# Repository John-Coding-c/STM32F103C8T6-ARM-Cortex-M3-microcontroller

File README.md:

# STM32 PCB

STM32F103C8T6 breakout board — USB-powered, SWD/UART/I2C headers, 41 × 31 mm, 2 layers. KiCad 10.

## Specs

- **MCU:** STM32F103C8T6, Cortex-M3 @ 72 MHz, 64 KB flash, 20 KB RAM, LQFP-48
- **Clock:** 16 MHz HSE crystal (3225), 2× 10 pF load caps
- **Power:** 5 V USB VBUS → AMS1117-3.3 LDO (1 A, SOT-223), 22 µF in/out
- **Decoupling:** 5× 100 nF (0402) + 10 µF bulk on VDD
- **VDDA:** filtered via 120 Ω ferrite bead + 10 nF + 1 µF
- **USB:** full-speed device on PA11/PA12, 1.5 kΩ D+ pull-up
- **Boot:** SPDT slide switch on BOOT0 via 10 kΩ
- **I2C pull-ups:** 1.5 kΩ to 3.3 V
- **Indicator:** red power LED (0603), 1.5 kΩ (~1 mA)
- **Mounting:** 4× 2.1 mm holes (M2), 3 mm corner radius

## Schematic

## PCB

| Parameter | Value |
| --- | --- |
| Size | 41 × 31 mm |
| Stackup | 2-layer, 1.6 mm FR4, 35 µm Cu |
| Bottom layer | Solid GND pour |
| Min track / clearance | 0.2 / 0.2 mm |
| Power tracks | 0.5 mm |
| Vias | 0.6–0.7 mm / 0.3 mm drill |
| Components | 28 parts + 4 mounting holes, all top side |
| Passives | 0402 / 0603 / 0805 |

## Pinout

All headers 1×4, 2.54 mm. Pin 1 = square pad.

| Header | Pin 1 | Pin 2 | Pin 3 | Pin 4 |
| --- | --- | --- | --- | --- |
| SWD (J3) | 3.3 V | SWDIO / PA13 | SWCLK / PA14 | GND |
| UART (J1) | 3.3 V | TX / PB6 | RX / PB7 | GND |
| I2C (J2) | 3.3 V | SCL / PB10 | SDA / PB11 | GND |

- UART uses remapped USART1 — set `AFIO_MAPR_USART1_REMAP` in firmware.

## BOM

| Ref | Qty | Value | Package |
| --- | --- | --- | --- |
| U2 | 1 | STM32F103C8T6 | LQFP-48 |
| U1 | 1 | AMS1117-3.3 | SOT-223 |
| Y1 | 1 | 16 MHz | 3225-4 |
| J4 | 1 | Micro-USB B (Würth 629105150521) | SMD |
| J1–J3 | 3 | 1×4 header | 2.54 mm THT |
| SW1 | 1 | SPDT slide (C&K PCM12) | SMD |
| D1 | 1 | Red LED | 0603 |
| FB1 | 1 | 120 Ω ferrite | 0603 |
| C1, C2 | 2 | 22 µF | 0805 |
| C3 | 1 | 10 µF | 0603 |
| C4, C6, C7, C9, C10 | 5 | 100 nF | 0402 |
| C5, C8 | 2 | 10 pF | 0402 |
| C11 | 1 | 10 nF | 0402 |
| C12, C13 | 2 | 1 µF | 0402 |
| R1–R3, R5 | 4 | 1.5 kΩ | 0402 |
| R4 | 1 | 10 kΩ | 0402 |

- LCSC part numbers included — ready for JLCPCB assembly.
- Full files: `STM32-BOM.csv`, `STM32-all-pos.csv`

## Files

```
STM32.kicad_pro / .kicad_sch / .kicad_pcb   KiCad project
STM32-BOM.csv, STM32-all-pos.csv            BOM + pick-and-place
629105150521 (rev1).stp                     USB connector 3D model
manufracture/                               Gerbers + drill
images/                                     Render + schematic
```

## Programming

- **SWD:** ST-Link V2 → J3. Flash with STM32CubeProgrammer or OpenOCD.
- **Bootloader:** BOOT0 = 1 enters the ROM bootloader.

## License

[CERN-OHL-P-2.0](https://ohwr.org/cern_ohl_p_v2.txt) — permissive open hardware license. See `LICENSE`.

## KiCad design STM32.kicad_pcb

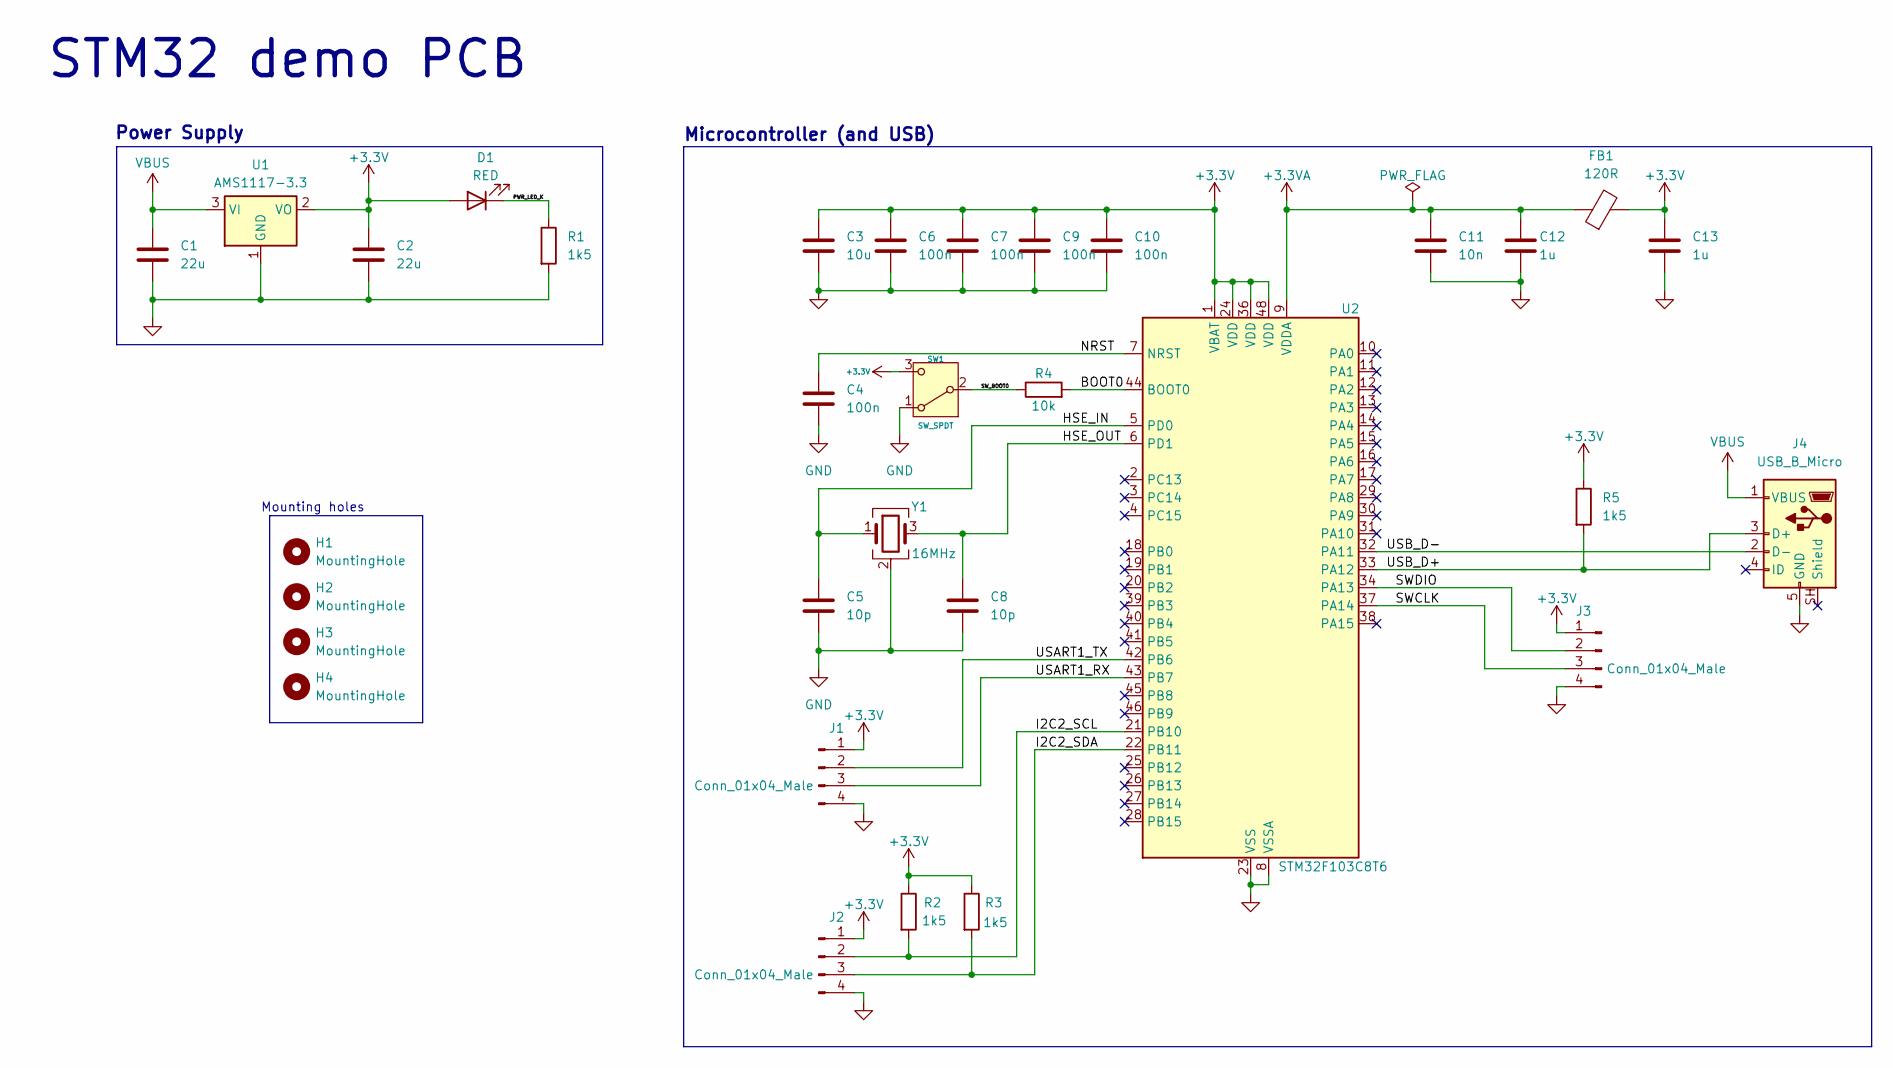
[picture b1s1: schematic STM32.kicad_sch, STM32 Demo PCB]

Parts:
C1, C2: 22u; C_0805_2012Metric; LCSC C45783
C3: 10u; C_0603_1608Metric; LCSC C19702
C4, C6, C7, C9, C10: 100n; C_0402_1005Metric; LCSC C1525
C5, C8: 10p; C_0402_1005Metric; LCSC C32949
C11: 10n; C_0402_1005Metric; LCSC C15195
C12, C13: 1u; C_0402_1005Metric; LCSC C52923
D1: RED; LED_0603_1608Metric; LCSC C2286
FB1: 120R; L_0603_1608Metric
H1, H2, H3, H4: MountingHole; MountingHole_2.1mm
J1, J2, J3: Conn_01x04_Male; PinHeader_1x04_P2.54mm_Vertical
J4: USB_B_Micro; USB_Micro-B_Wuerth_629105150521
R1, R2, R3, R5: 1k5; R_0402_1005Metric; LCSC C25867
R4: 10k; R_0402_1005Metric; LCSC C25744
SW1: SW_SPDT; SW_SPDT_PCM12; LCSC C221841
U1: AMS1117-3.3; SOT-223-3_TabPin2; LCSC C6186
U2: STM32F103C8T6; LQFP-48_7x7mm_P0.5mm; LCSC C8734
Y1: 16MHz; Crystal_SMD_3225-4Pin_3.2x2.5mm; LCSC C13738

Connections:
+3.3V: C2.1, C3.1, C6.1, C7.1, C9.1, C10.1, C13.1, D1.2 (A), FB1.2, J1.1, J2.1, J3.1, R2.1, R3.1, R5.1, SW1.3 (C), U1.2 (VO), U2.1 (VBAT), U2.24 (VDD), U2.36 (VDD), U2.48 (VDD)
+3.3VA: C11.1, C12.1, FB1.1, U2.9 (VDDA)
/BOOT0: R4.2, U2.44 (BOOT0)
/HSE_IN: C5.2, U2.5 (PD0), Y1.1
/HSE_OUT: C8.2, U2.6 (PD1), Y1.3
/I2C2_SCL: J2.2, R2.2, U2.21 (PB10)
/I2C2_SDA: J2.3, R3.2, U2.22 (PB11)
/NRST: C4.1, U2.7 (NRST)
/PWR_LED_K: D1.1 (K), R1.1
/SWCLK: J3.3, U2.37 (PA14)
/SWDIO: J3.2, U2.34 (PA13)
/SW_BOOT0: R4.1, SW1.2 (B)
/USART1_RX: J1.3, U2.43 (PB7)
/USART1_TX: J1.2, U2.42 (PB6)
/USB_D+: J4.3 (D+), R5.2, U2.33 (PA12)
/USB_D-: J4.2 (D-), U2.32 (PA11)
GND: C1.2, C2.2, C3.2, C4.2, C5.1, C6.2, C7.2, C8.1, C9.2, C10.2, C11.2, C12.2, C13.2, J1.4, J2.4, J3.4, J4.5 (GND), R1.2, SW1.1 (A), U1.1 (GND), U2.8 (VSSA), U2.23 (VSS), U2.35 (VSS), U2.47 (VSS), Y1.2 (G), Y1.4 (G)
VBUS: C1.1, J4.1 (VBUS), U1.3 (VI)

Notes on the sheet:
STM32 demo PCB
Mounting holes
Microcontroller (and USB)
Power Supply

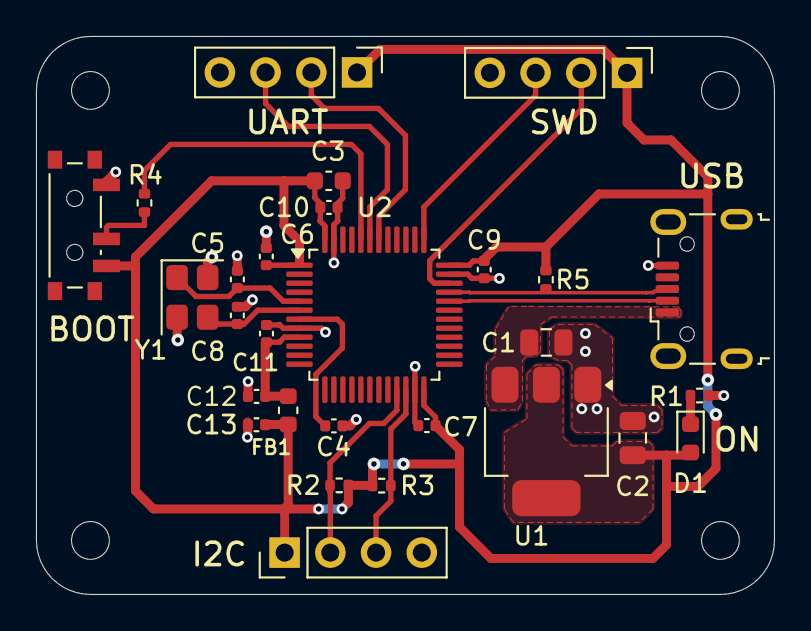
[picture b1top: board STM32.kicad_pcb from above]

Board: 2 copper layers, 41.0 x 31.0 mm, 32 parts (0 on the bottom side), 18 nets.

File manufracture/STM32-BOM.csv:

"Reference","Qty","Value","DNP","Footprint","Datasheet"
"C1,C2","2","22u","","Capacitor_SMD:C_0805_2012Metric",""
"C3","1","10u","","Capacitor_SMD:C_0603_1608Metric",""
"C4,C6,C7,C9,C10","5","100n","","Capacitor_SMD:C_0402_1005Metric",""
"C5,C8","2","10p","","Capacitor_SMD:C_0402_1005Metric",""
"C11","1","10n","","Capacitor_SMD:C_0402_1005Metric",""
"C12,C13","2","1u","","Capacitor_SMD:C_0402_1005Metric",""
"D1","1","RED","","LED_SMD:LED_0603_1608Metric",""
"FB1","1","120R","","Inductor_SMD:L_0603_1608Metric",""
"J1,J2,J3","3","Conn_01x04_Male","","Connector_PinHeader_2.54mm:PinHeader_1x04_P2.54mm_Vertical",""
"J4","1","USB_B_Micro","","Connector_USB:USB_Micro-B_Wuerth_629105150521",""
"R1,R2,R3,R5","4","1k5","","Resistor_SMD:R_0402_1005Metric",""
"R4","1","10k","","Resistor_SMD:R_0402_1005Metric",""
"SW1","1","SW_SPDT","","Button_Switch_SMD:SW_SPDT_PCM12",""
"U1","1","AMS1117-3.3","","Package_TO_SOT_SMD:SOT-223-3_TabPin2","http://www.advanced-monolithic.com/pdf/ds1117.pdf"
"U2","1","STM32F103C8T6","","Package_QFP:LQFP-48_7x7mm_P0.5mm","https://www.st.com/resource/en/datasheet/stm32f103c8.pdf"
"Y1","1","16MHz","","Crystal:Crystal_SMD_3225-4Pin_3.2x2.5mm",""
